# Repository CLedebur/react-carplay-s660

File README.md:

# S660 CarPlay

An open-source CarPlay head unit for the Honda S660, built on a Raspberry Pi Compute Module 4 (CM4) + Oratek TOFU carrier board. CarPlay runs as a web app ([`carplay-web-app`](hardware/path-b/node-CarPlay/), built on [node-CarPlay](https://github.com/rhysmorgan134/node-CarPlay)) in the Pi's own Chromium, full-screen under the `cage` kiosk compositor, customised for the S660's panel, controls, and boot environment.

Hardware assembly, wiring, and enclosure instructions are covered separately. This document is the software-side getting-started guide: how to provision a Pi into a working head unit, and how to develop on it.

## Current status

The Pi's system Chromium **composites on the GPU and decodes the CarPlay H.264 stream in hardware**. Measured 2026-09-12 with CarPlay streaming, Chromium's GPU process holds `/dev/video10`, the CM4's `bcm2835-codec` decoder. Raspberry Pi's Chromium build carries the V4L2 patches, and the web app's WebCodecs decoder picks them up with no extra flags (BUILD_NOTES §8.5, §27.1). The kiosk is on screen about 2.5 s after the kernel starts. Logs from every drive are kept on a dedicated `/persist` partition (§31).

> **Path A retired (2026-10-07).** This repo started as a fork of [react-carplay](https://github.com/rhysmorgan134/react-carplay), an Electron app. Upstream Electron lacks the Pi's GPU/V4L2 patches, so it could only render and decode in software. It has been removed in favour of the web app, which is much faster. The last commit containing it is tagged [`path-a-final`](https://github.com/CLedebur/react-carplay-s660/tree/path-a-final), including its CAN-bus, MOST and key-binding code (BUILD_NOTES §32). You will still see "Path A" and "Path B" in the build notes. That history is kept on purpose.

For the full build history, every non-obvious fix, and the reasoning behind each decision, read [`hardware/BUILD_NOTES.md`](hardware/BUILD_NOTES.md) — it is the source of truth for anything hardware-, boot-, or GPU-related.

For PCB design work with the KiCad MCP server in VS Code/Copilot, see
[`pdb-circuit/README.md`](pdb-circuit/README.md).

# Getting started

This is the fastest path to a working unit and is how the reference build is set up.

## Hardware

- A Raspberry Pi Compute Module 4 flashed with **Raspberry Pi OS Lite (64-bit)**, currently Debian 13 "Trixie", with at least 4GB RAM.
- Oratek TOFU Board [(link)](https://store.oratek.com/products/tofu-electronic-board)
- Oratek M.2 Adapter [(link)](https://store.oratek.com/products/tofu-m-2-key-m-adapter)
- CM4 Heatsink/Fan [(link)](https://pt.aliexpress.com/item/1005002541607239.html)
- Carlinkit CPC200-CCPA/CCPM dongle. This performs the Apple MFi handshake, so an iPhone cannot be plugged directly into the Pi. [(link)](https://www.amazon.es/dp/B0H7GRL6YJ)
- HDMI-e to HDMI cable 0.5m [(example)](https://pt.aliexpress.com/item/1005005903047904.html)
- Honda S660 Option Coupler (required for providing power to the CM4 + board). A Pikaichi TR-196 is ideal if you can find one. Otherwise, you will want a branching coupler so that you can accommodate more peripherals in the future. This is what I got, though I wasn't able to find a branching type coupler: [(example)](https://www.amazon.co.jp/-/en/Pikachi-Power-Supply-Optional-Coupler/dp/B0116HSI40)
- Voltage Converter/Stabilizer (8V-40V to 12V 3A 36W) to provide the board with clean power. [(example)](https://www.amazon.es/dp/B0CPSLSH4J)
- **Not required but highly recommended** - NVMe M.2 SSD (as it will greatly improve boot times and hold up better than an eMMC).
- A MicroSD card (at least 16GB) to flash the Pi OS Lite image onto the CM4. 
- 2.1mm barrel jack AC adapter [(link)](https://www.amazon.es/dp/B09K59PGZ5)
- Wi-Fi Antenna (if you want to use Wi-Fi instead of Ethernet). [(example)](https://www.amazon.es/dp/B08RRX9H2Q)
- 3D-Printed case (pending)

### Assembly

1. Using the standoffs provided by the heatsink/fan kit between the CM4 and the TOFU board, mount the CM4 to the TOFU board. This will allow the heatsink/fan to be mounted on top of the CM4 without bending the CM4.
2. Insert the MicroSD card into the CM4 and flash the Raspberry Pi OS Lite (64-bit) image onto it. You can use [Raspberry Pi Imager](https://www.raspberrypi.com/software/) to do this.
3. Insert the NVMe M.2 SSD into the M.2 adapter first, and then insert onto the TOFU board, and then mount.
4. Connect a monitor to the HDMI port, and a keyboard to the TOFU board. Power on the board and complete the initial setup of the Raspberry Pi OS Lite (64-bit) image. Make sure to enable SSH and set a username and password.
5. Connect the Carlinkit dongle to the USB port on the TOFU board.
6. Run the provisioning script (see below) to install the software and configure the system.

## Software

**Run the provisioning script**, as your normal user (not root, not with `sudo` —
it calls `sudo` itself where needed):

```bash
git clone https://github.com/CLedebur/react-carplay-s660.git
cd react-carplay-s660/hardware
chmod +x provision.sh
./provision.sh
```

This installs the web app as `carplay.service`, enabled to start at boot. The script is safe to re-run after a failure. It ends with **a required reboot**. Starting the kiosk service live (`systemctl start`) does not reliably set up the VT/seat session on first setup. That reboot also runs the one-shot `/persist` repartition (BUILD_NOTES §31), so keep the Pi on stable power for it.

# Physical Installation

## Modifying the head unit

Using plastic trim removal tools, remove the S660's interior parts in this order:

1. Glove box
2. AC vent behind glove box
3. Panels on both sides of the center console in the footwells
4. Remove the plastic shroud behind the center screen, and then unscrew the bolts. Unplug the proprietary HDMI-e cable (gray) and remove the screen.
5. The frame around the stick shift. No need to pull it off entirely, just enough to remove the frame around the center console. The frame is held in place by clips, so be careful not to break them.
6. The tray behind the stick shift. It is held in place with clips. Gently pry the tray up and pull it out. Be careful not to break the clips. Disconnect the cables for the buttons and set aside.
7. The center console itself. It is held in place with clips. Gently pry the front of the console up and pull it out. Be careful not to break the clips. Disconnect the cables for the buttons and set aside.
8. Unscrew the two 10mm bolts securing the head unit to the dashboard. Do not remove, only loosen them.
9. Slide the head unit out sideways; it will slide out of the compartment where the glove box was. Disconnect the cables as you go. Try not to disconnect as many cables you can, as it's very difficult to reconnect them.
10. When you're able to reach it, unplug the HDMI-e cable on the far right side of the head unit (it is the black one) and set aside. Plug in the new HDMI-e cable and route it down to the cavity in the center console behind the shifter.
11. Re-insert the head unit, reconnecting the cables along the way, EXCEPT for the 24-pin harness at the far left. Pull out the harness as much as you can, and then strip away some of the electrical tape to expose around 5mm of the wire coming from pin 22. It will be the light green wire on the bottom left.
12. Cut the wire 5mm from the plug, and then solder the wire from the plug to a small length of wire that will reach a screw on the left side of the head unit. If done correctly, this will bypass the handbrake signal and allow the head unit to work while driving. Make sure to insulate the soldered connection with heat shrink or electrical tape.
13. Plug in the harness and test the head unit. If it works, reassemble the glove box and the AC vent behind it. If it doesn't work, check the soldered connection and make sure the wire is connected to the screw on the left side of the head unit.

## Powering the Pi

1. Wire the 8v-40v to 12v converter to the option coupler. You will want about 1.5m of wire to reach the center console. The converter can be kept in the cavity behind the stick shift. Ensure you connect the positive wire to port number five on the coupler (IGN power). The negative wire will be connected to the chassis ground.
2. Follow [these instructions](https://minkara.carview.co.jp/userid/135377/car/3279425/6972067/note.aspx) to install the option coupler behind the driver's side AC vent.
3. Route the wire behind the carpet. Make sure you secure the wire with zip ties to prevent them from getting caught up in the pedals.
4. Route the wire to the cavity under the center console, and connect to the red/black wire pair on the converter.
5. Connect the industrial connector provided by the TOFU board to the yellow/black wire pair on the converter.
6. Plug in the industrial connecetor to the Pi and start the car to test the power. The Pi should boot up.
7. Switch the input to HDMI via the button on the steering wheel if it isn't there already. The Pi should be running the CarPlay app.

# Works in Progress

1. 3D-printed case for the Pi + TOFU board sized to fit the S660's center console with mounting points.
2. Man-in-the-Middle (MITM) proxy for the physical buttons on the center console so that the buttons and knob can be used to control the CarPlay app ([`hardware/opera-mitm/`](hardware/opera-mitm/), BUILD_NOTES §30).
3. CAN-bus connection, to build vehicle data and the car's own views into the web app.
4. (eventually) A replacement screen for the S660 with touchscreen capabilities and a higher resolution than the stock screen.

# Script Details

**What the script does**, in short (see the script's own comments and
`hardware/BUILD_NOTES.md` §4, §22, §24, and §29 for the full reasoning):

- Trims ~10s off boot by disabling cloud-init, unneeded timers/services, swap, and the
  firmware's own initramfs auto-detection, and by quieting the kernel console.
- Enables Overlay FS: the real root filesystem is mounted read-only underneath a writable
  tmpfs layer, so a hard power cut — this car's normal shutdown path, via ignition, on every
  drive — can't corrupt it. Needs an initramfs to actually run (that's what the auto-detection
  above skips; this one is loaded explicitly instead), which is installed and built during
  provisioning. `/boot/firmware` stays normally writable throughout — verified against a real
  hard power cut (`BUILD_NOTES.md` §29).
- Shrinks root to 64 GiB once and gives the rest of the disk to a `/persist` partition,
  which the overlay does not cover. The systemd journal and the last-known clock live there,
  so every drive's logs survive the ignition cutting power (`BUILD_NOTES.md` §31).
- Installs `cage` (Wayland kiosk compositor) + `seatd`, the udev rule that gives the
  Carlinkit dongle non-root USB/WebUSB access, and a Chromium managed policy that
  pre-grants the dongle to the kiosk page — no on-screen authorisation, ever, even after a
  browser-profile reset (BUILD_NOTES §28).
- Installs system Chromium and builds this repo's vendored `node-CarPlay`/`carplay-web-app`
  source.
- Writes and enables the systemd unit that launches the kiosk on boot.
- Preloads the HDMI component drivers and overlaps the web server and compositor startup.
  (An earlier version of this also shipped an auto-refreshed uncompressed kernel image for
  a further ~2s savings; reverted after a field failure — see `BUILD_NOTES.md` §26.)
- Starts host Bluetooth after 15 s for the trackpad, including when Chromium requests
  BlueZ through D-Bus. Pairing data and the Bluetooth radio remain available.

**By design, networking is requested 20 s after Linux starts**, and timer coalescing
can delay it further. Nothing on the boot-critical path depends on the network,
since Wi-Fi is never guaranteed inside the car. Don't "fix" this; it's intentional.
If the Pi seems unreachable right after a reboot, give it a minute.

## Developing the app

The app source is the `node-carplay` library plus `carplay-web-app`, modified from upstream
[`rhysmorgan134/node-CarPlay`](https://github.com/rhysmorgan134/node-CarPlay) (MIT). It is
vendored directly into this repo at
[`hardware/path-b/node-CarPlay/`](hardware/path-b/node-CarPlay/). It is not a separate
clone or an npm/git dependency. Edit it in place, rebuild, and redeploy by pulling this
repo onto the Pi; the kiosk serves
`~/react-carplay-s660/hardware/path-b/node-CarPlay/examples/carplay-web-app`. See that
directory's own `README.md` and `hardware/BUILD_NOTES.md` §11 and §23 for the exact
build/deploy commands and toolchain gotchas.

**Overlay FS is on in normal use**, so changes made on the Pi vanish at the next power-off.
Turn it off before you deploy (BUILD_NOTES §29), and turn it back on afterwards.

## Thanks

This project builds on [node-carplay](https://github.com/rhysmorgan134/node-CarPlay) and
began as a fork of [react-carplay](https://github.com/rhysmorgan134/react-carplay), both by
Rhys Morgan, with significant CarPlay improvements contributed upstream by @gozmanyoni and
@steelbrain.

If you'd like to show them appreciation, you can [buy gozmanyoni a coffee](https://www.buymeacoffee.com/ygoz) or [buy Rhys a coffee](https://www.buymeacoffee.com/rhysm).

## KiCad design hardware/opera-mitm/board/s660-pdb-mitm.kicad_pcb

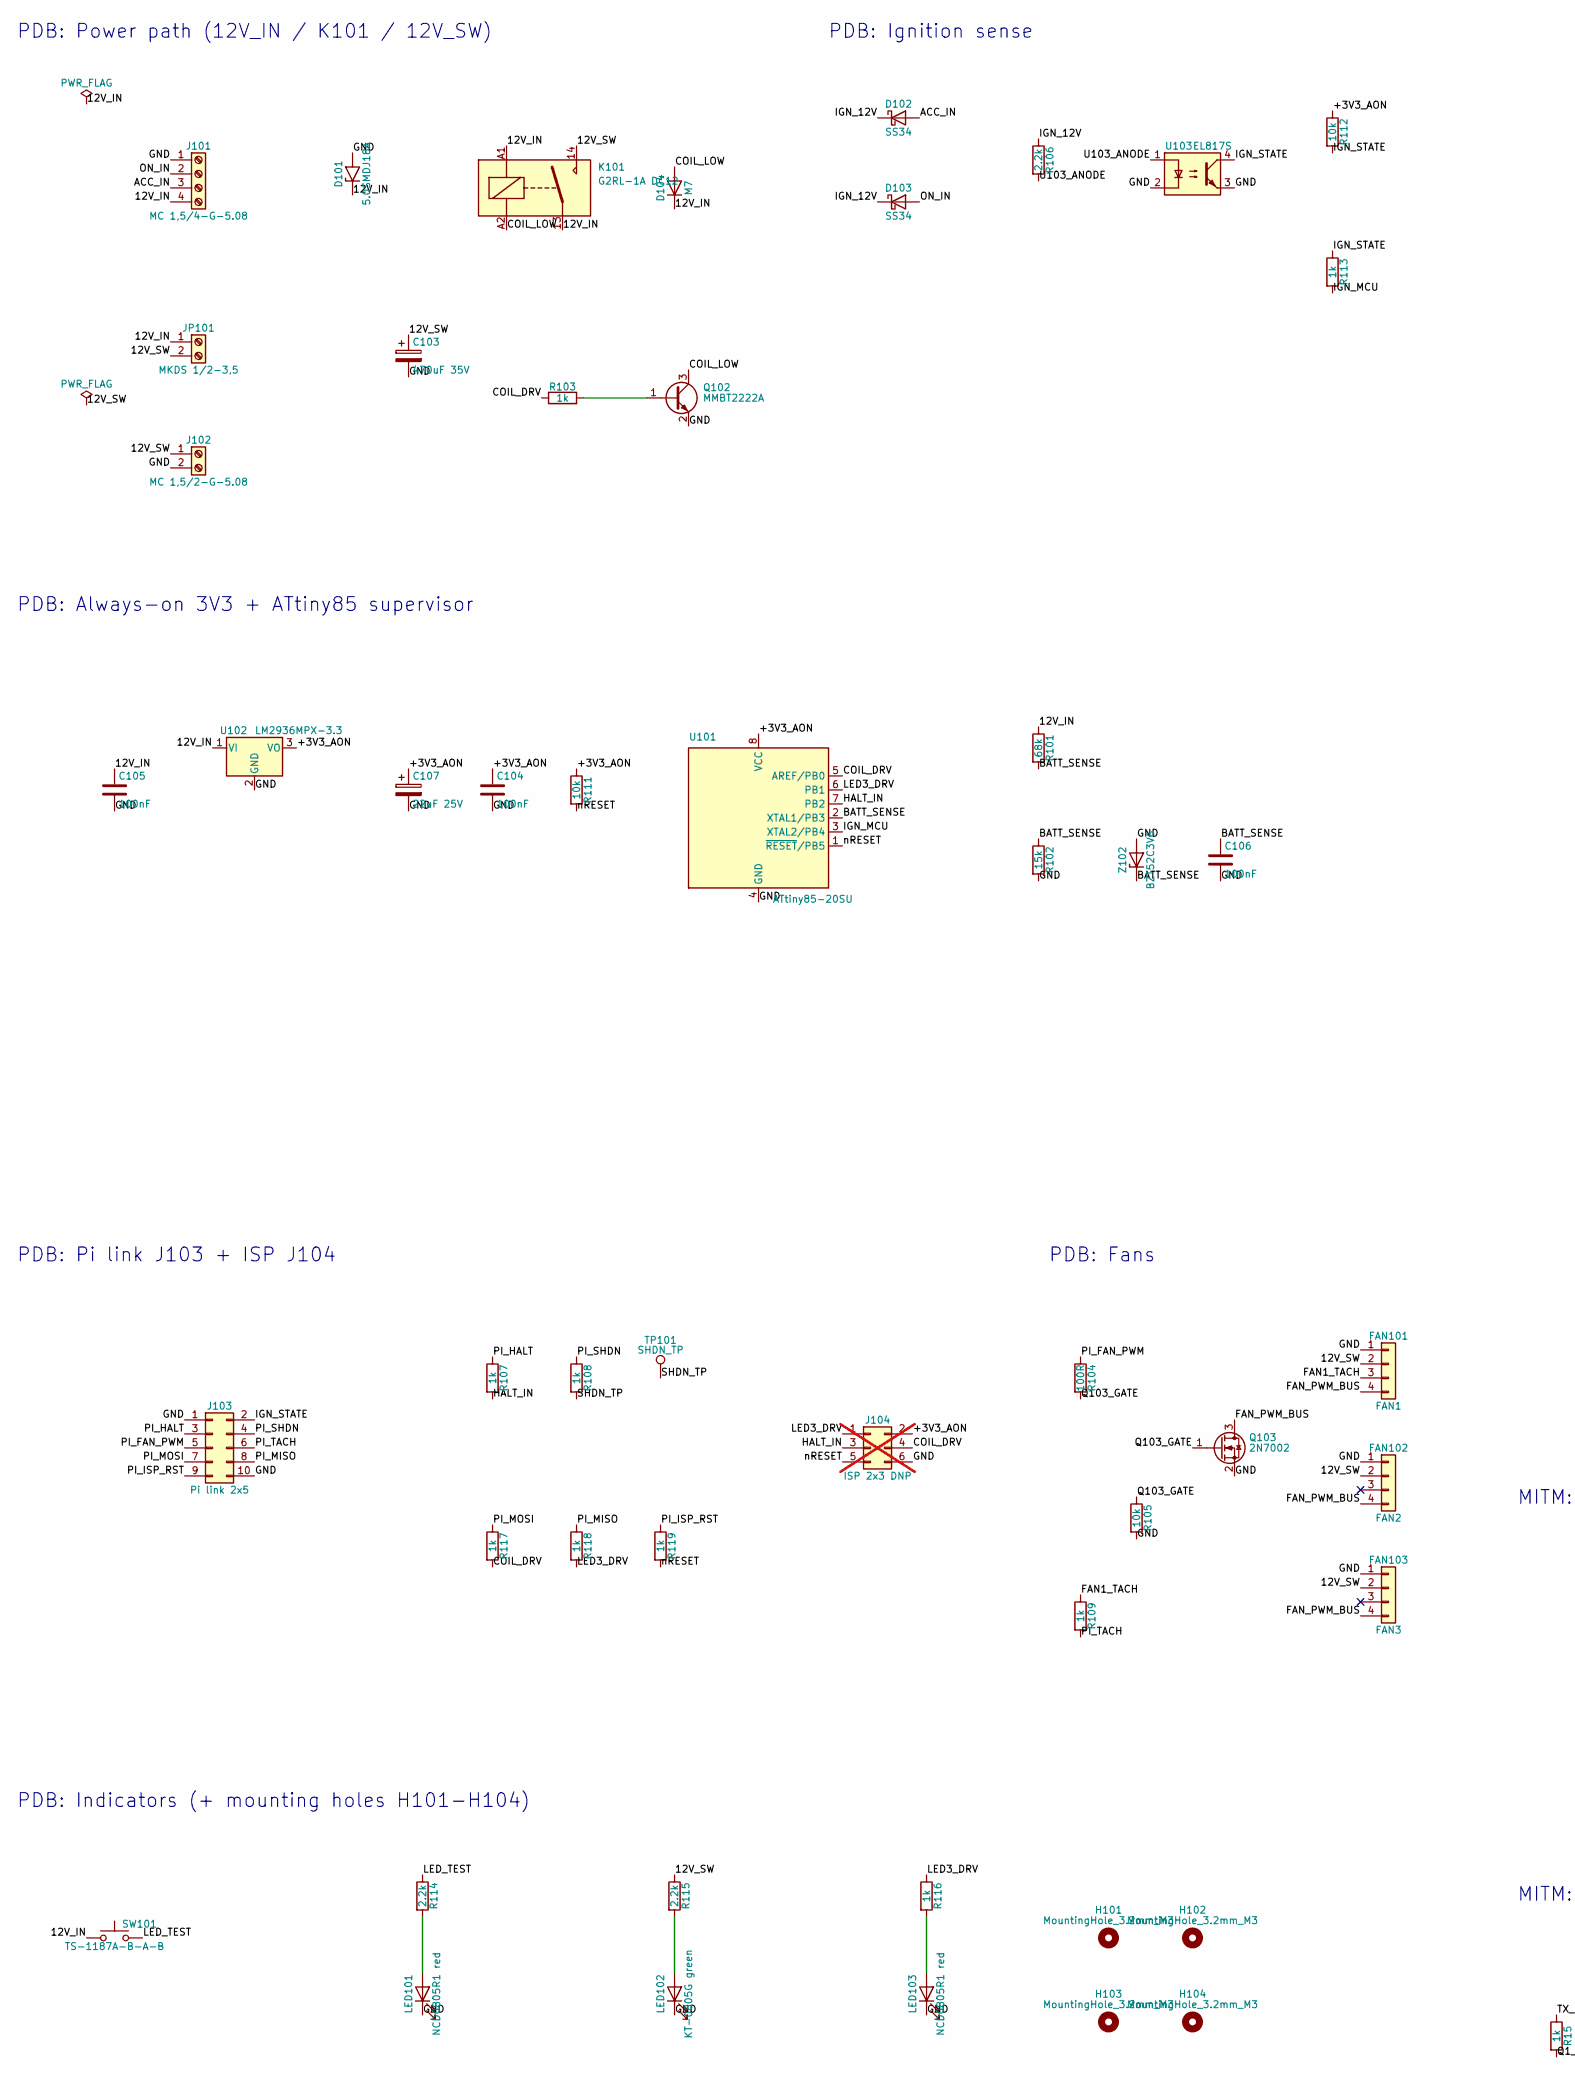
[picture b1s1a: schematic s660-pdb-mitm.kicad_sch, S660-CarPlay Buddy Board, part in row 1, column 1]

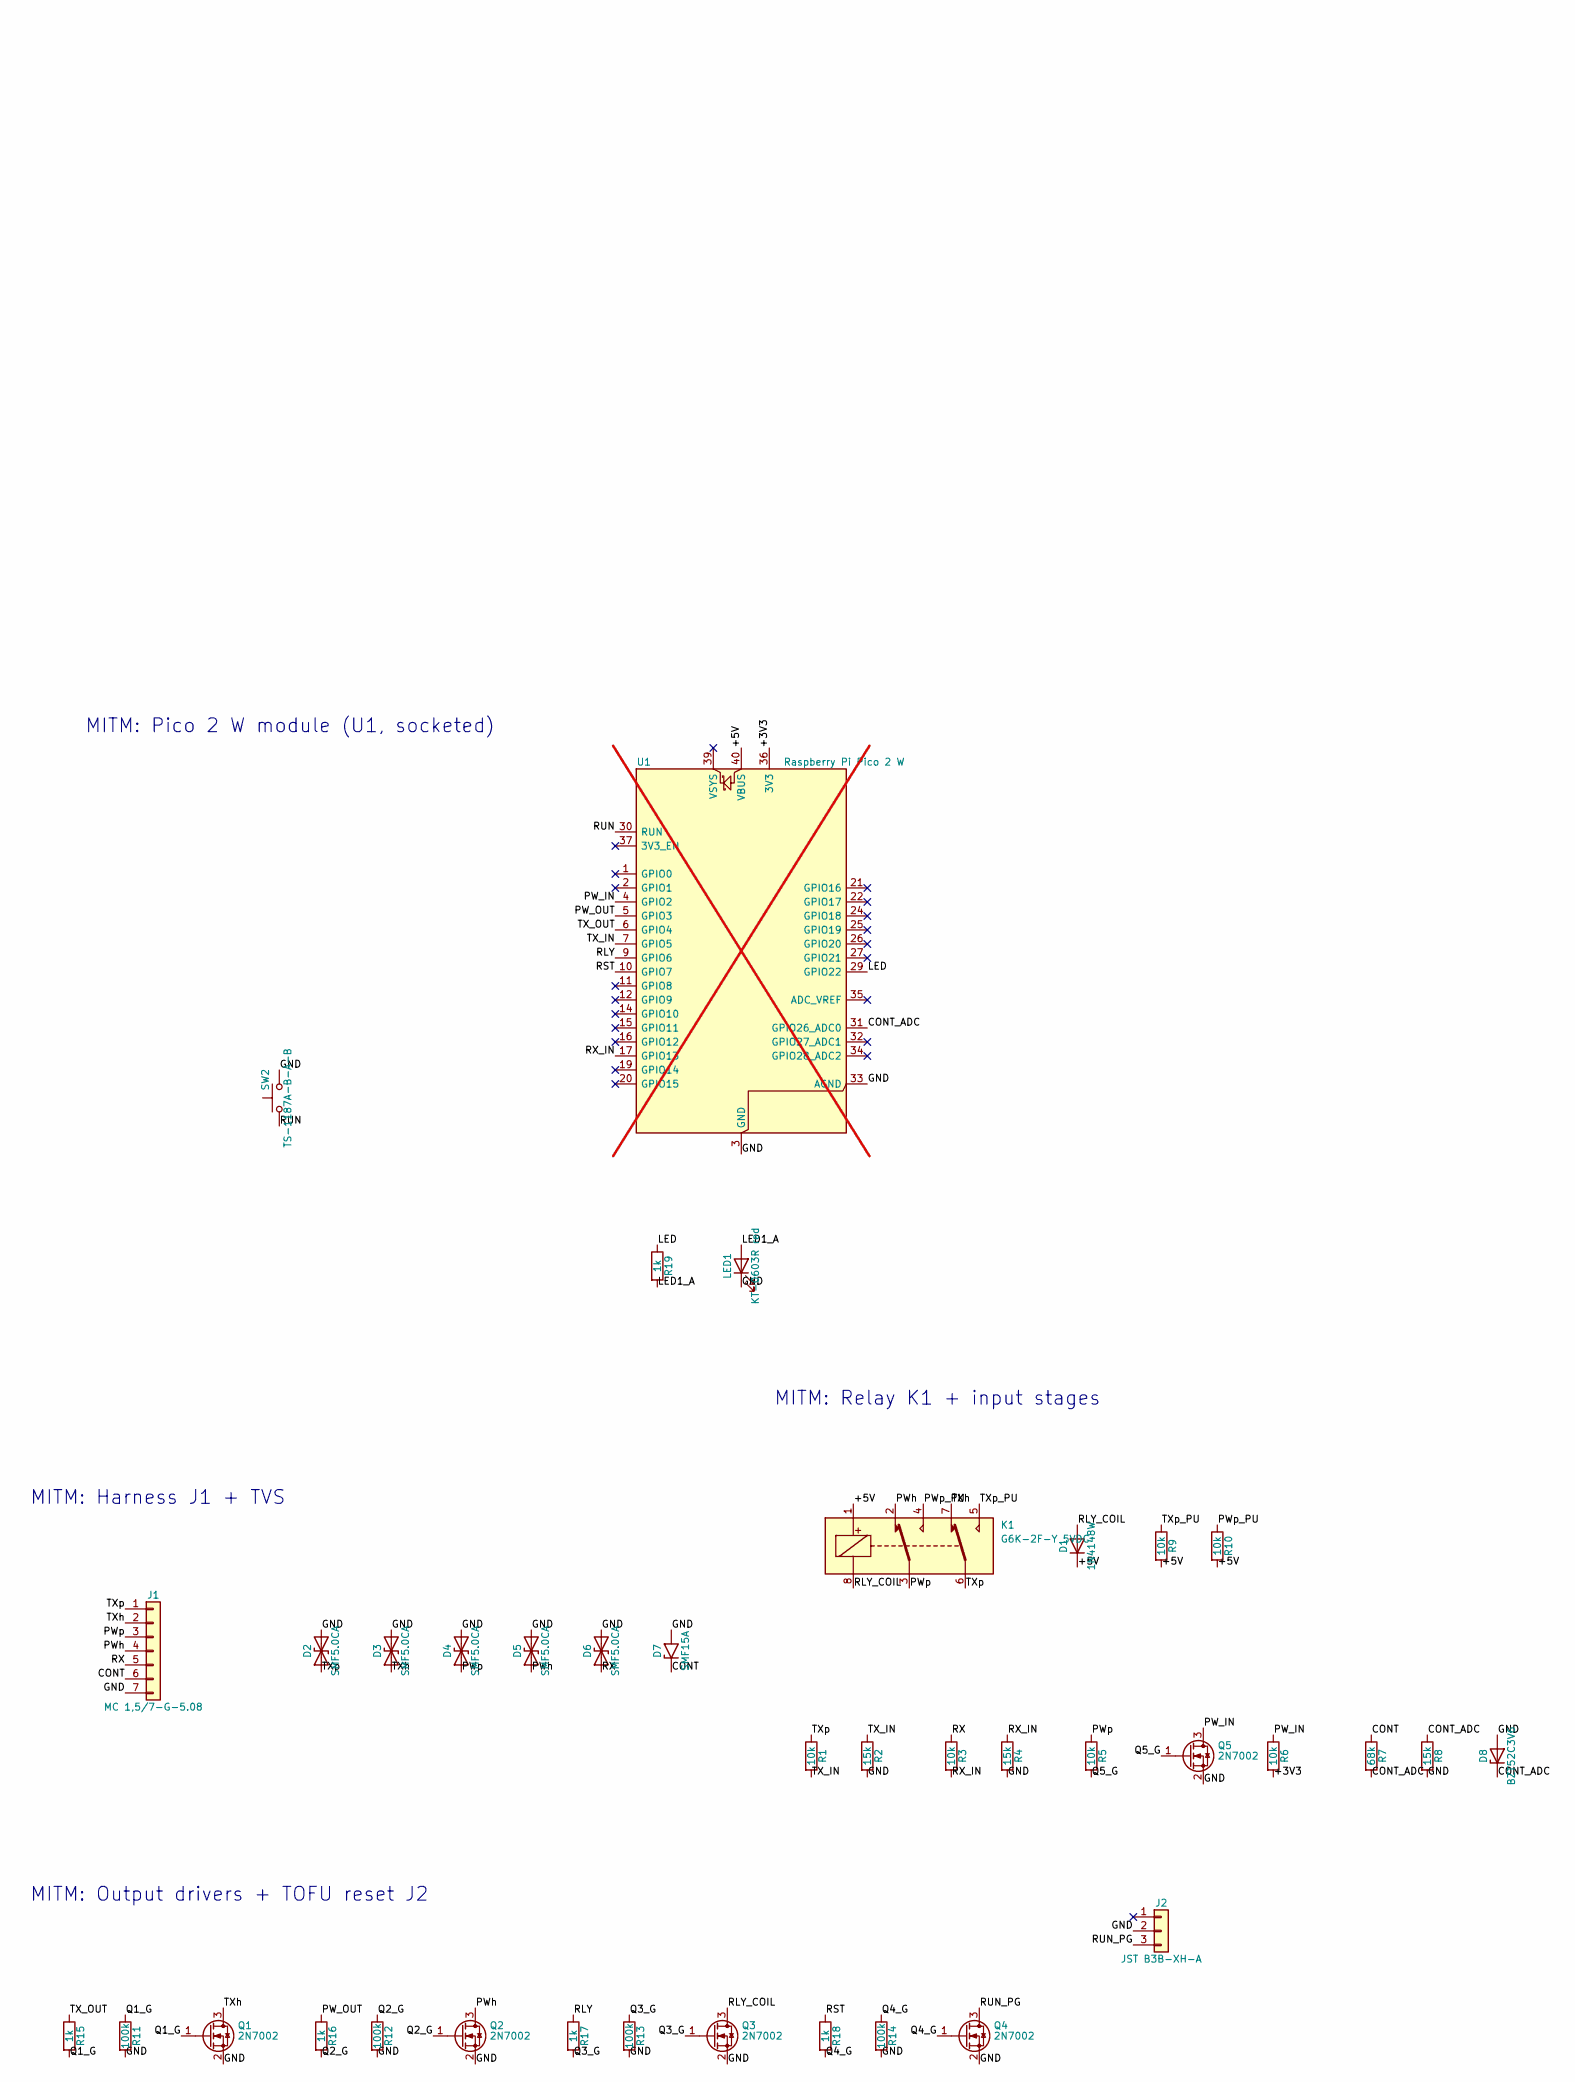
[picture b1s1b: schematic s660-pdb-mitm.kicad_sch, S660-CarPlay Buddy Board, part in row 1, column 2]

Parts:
C103: 470uF 35V; CP_Elec_8x10.5; MPN RV35V470M8X10; LCSC C48935389
C104, C105, C106: 100nF; C_0603_1608Metric; LCSC C14663
C107: 22uF 25V; CP_EIA-6032-28_Kemet-C; MPN TAJC226K025RNJ; LCSC C7214
D1: 1N4148W; D_SOD-123; MPN 1N4148W; LCSC C81598
D2, D3, D4, D5, D6: SMF5.0CA; D_SOD-123F; MPN SMF5.0CA; LCSC C19077498
D7: SMF15A; D_SOD-123F; MPN SMF15A; LCSC C19077509
D8: BZT52C3V6; D_SOD-123; MPN BZT52C3V6; LCSC C19077397
D101: 5.0SMDJ18A; D_SMC; MPN 5.0SMDJ18A; LCSC C2842368
D102, D103: SS34; D_SMA; MPN SS34; LCSC C8678
D104: M7; D_SMA; MPN M7; LCSC C7420350
FAN101: FAN1; PinHeader_1x04_P2.54mm_Horizontal
FAN102: FAN2; PinHeader_1x04_P2.54mm_Horizontal
FAN103: FAN3; PinHeader_1x04_P2.54mm_Horizontal
H101, H102, H103, H104: MountingHole_3.2mm_M3
J1: MC 1,5/7-G-5.08; PhoenixContact_MC_1,5_7-G-5.08_1x07_P5.08mm_Horizontal; MPN MC 1,5/7-G-5.08 (1836231)
J2: JST B3B-XH-A; JST_XH_B3B-XH-A_1x03_P2.50mm_Vertical; MPN B3B-XH-A; LCSC C144394
J101: MC 1,5/4-G-5.08; PhoenixContact_MC_1,5_4-G-5.08_1x04_P5.08mm_Horizontal; MPN MC 1,5/4-G-5.08
J102: MC 1,5/2-G-5.08; PhoenixContact_MC_1,5_2-G-5.08_1x02_P5.08mm_Horizontal; MPN MC 1,5/2-G-5.08
J103: Pi link 2x5; PinHeader_2x05_P2.54mm_Horizontal
J104: ISP 2x3 DNP; PinHeader_2x03_P2.54mm_Vertical; not fitted
JP101: MKDS 1/2-3,5; Phoenix_MKDS_1_2_3.5_1751248; MPN 1751248
K1: G6K-2F-Y 5VDC; Relay_DPDT_Omron_G6K-2F-Y; MPN G6K-2F-Y 5VDC; LCSC C2982926
K101: G2RL-1A DC12; Relay_SPST_Omron_G2RL-1A; MPN G2RL-1A DC12
LED1: KT-0603R red; LED_0603_1608Metric; MPN KT-0603R; LCSC C2286
LED101, LED103: NCD0805R1 red; LED_0805_2012Metric; MPN NCD0805R1; LCSC C84256
LED102: KT-0805G green; LED_0805_2012Metric; MPN KT-0805G; LCSC C2297
Q1, Q2, Q3, Q4, Q5, Q103: 2N7002; SOT-23; MPN 2N7002; LCSC C8545
Q102: MMBT2222A; SOT-23; MPN MMBT2222A; LCSC C8512
R1, R3, R5, R6, R9, R10, R105, R111, R112: 10k; R_0603_1608Metric; LCSC C25804
R2, R4, R8, R102: 15k; R_0603_1608Metric; LCSC C22809
R7, R101: 68k; R_0603_1608Metric; LCSC C23231
R11, R12, R13, R14: 100k; R_0603_1608Metric; LCSC C25803
R15, R16, R17, R18, R19, R103, R107, R108, R109, R113, R116, R117, R118, R119: 1k; R_0603_1608Metric; LCSC C21190
R104: 100R; R_0603_1608Metric; LCSC C22775
R106, R114, R115: 2.2k; R_0603_1608Metric; LCSC C4190
SW2, SW101: TS-1187A-B-A-B; SW_Push_1P1T_XKB_TS-1187A; MPN TS-1187A-B-A-B; LCSC C318884
TP101: SHDN_TP; TestPoint_Pad_D1.5mm
U1: Raspberry Pi Pico 2 W; RaspberryPi_Pico_Common_THT; MPN SC1634; not fitted
U101: ATtiny85-20SU; SOIC-8_5.3x5.3mm_P1.27mm; MPN ATtiny85-20SU; LCSC C31540447
U102: LM2936MPX-3.3; SOT-223-3_TabPin2; MPN LM2936MPX-3.3; LCSC C2872050
U103: EL817S; SOP-4_3.8x4.1mm_P2.54mm; MPN EL817S; LCSC C63268
Z102: BZT52C3V6; D_SOD-123; MPN BZT52C3V6; LCSC C19077397

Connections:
/+3V3: R6.2, U1.36 (3V3)
/+3V3_AON: C104.1, C107.1, J104.2, R111.1, R112.1, U101.8 (VCC), U102.3 (VO)
/+5V: D1.1 (K), K1.1, R9.2, R10.2, U1.40 (VBUS)
/ACC_IN: D102.2 (A), J101.3
/BATT_SENSE: C106.1, R101.2, R102.1, U101.2 (XTAL1/PB3), Z102.1 (K)
/COIL_DRV: J104.4, R103.1, R117.2, U101.5 (AREF/PB0)
/COIL_LOW: D104.2 (A), K101.A2, Q102.3 (C)
/CONT: D7.1 (A1), J1.6, R7.1
/CONT_ADC: D8.1 (K), R7.2, R8.1, U1.31 (GPIO26_ADC0)
/FAN1_TACH: FAN101.3, R109.1
/FAN_PWM_BUS: FAN101.4, FAN102.4, FAN103.4, Q103.3 (D)
/GND: C103.2, C104.2, C105.2, C106.2, C107.2, D2.2 (A2), D3.2 (A2), D4.2 (A2), D5.2 (A2), D6.2 (A2), D7.2 (A2), D8.2 (A), D101.2 (A2), FAN101.1, FAN102.1, FAN103.1, J1.7, J2.2, J101.1, J102.2, J103.1, J103.10, J104.6, LED1.1 (K), LED101.1 (K), LED102.1 (K), LED103.1 (K), Q1.2 (S), Q2.2 (S), Q3.2 (S), Q4.2 (S), Q5.2 (S), Q102.2 (E), Q103.2 (S), R2.2, R4.2, R8.2, R11.2, R12.2, R13.2, R14.2, R102.2, R105.2, SW2.2, U1.3 (GND), U1.8 (GND), U1.13 (GND), U1.18 (GND), U1.23 (GND), U1.28 (GND), U1.33 (AGND), U1.38 (GND), U101.4 (GND), U102.2 (GND), U103.2, U103.3, Z102.2 (A)
/HALT_IN: J104.3, R107.2, U101.7 (PB2)
/IGN_12V: D102.1 (K), D103.1 (K), R106.1
/IGN_MCU: R113.2, U101.3 (XTAL2/PB4)
/IGN_STATE: J103.2, R112.2, R113.1, U103.4
/LED: R19.1, U1.29 (GPIO22)
/LED1_A: LED1.2 (A), R19.2
/LED3_DRV: J104.1, R116.1, R118.2, U101.6 (PB1)
/LED_TEST: R114.1, SW101.2
/ON_IN: D103.2 (A), J101.2
/PI_FAN_PWM: J103.5, R104.1
/PI_HALT: J103.3, R107.1
/PI_ISP_RST: J103.9, R119.1
/PI_MISO: J103.8, R118.1
/PI_MOSI: J103.7, R117.1
/PI_SHDN: J103.4, R108.1
/PI_TACH: J103.6, R109.2
/PW_IN: Q5.3 (D), R6.1, U1.4 (GPIO2)
/PW_OUT: R16.1, U1.5 (GPIO3)
/PWh: D5.1 (A1), J1.4, K1.2, Q2.3 (D)
/PWp: D4.1 (A1), J1.3, K1.3, R5.1
/PWp_PU: K1.4, R10.1
/Q1_G: Q1.1 (G), R11.1, R15.2
/Q2_G: Q2.1 (G), R12.1, R16.2
/Q3_G: Q3.1 (G), R13.1, R17.2
/Q4_G: Q4.1 (G), R14.1, R18.2
/Q5_G: Q5.1 (G), R5.2
/Q103_GATE: Q103.1 (G), R104.2, R105.1
/RLY: R17.1, U1.9 (GPIO6)
/RLY_COIL: D1.2 (A), K1.8, Q3.3 (D)
/RST: R18.1, U1.10 (GPIO7)
/RUN: SW2.1, U1.30 (RUN)
/RUN_PG: J2.3, Q4.3 (D)
/RX: D6.1 (A1), J1.5, R3.1
/RX_IN: R3.2, R4.1, U1.17 (GPIO13)
/SHDN_TP: R108.2, TP101.1 (1_1)
/TX_IN: R1.2, R2.1, U1.7 (GPIO5)
/TX_OUT: R15.1, U1.6 (GPIO4)
/TXh: D3.1 (A1), J1.2, K1.7, Q1.3 (D)
/TXp: D2.1 (A1), J1.1, K1.6, R1.1
/TXp_PU: K1.5, R9.1
/U103_ANODE: R106.2, U103.1
/nRESET: J104.5, R111.2, R119.2, U101.1 (~RESET/PB5)
unnamed: LED101.2 (A), R114.2
unnamed: LED102.2 (A), R115.2
unnamed: LED103.2 (A), R116.2
unnamed: Q102.1 (B), R103.2

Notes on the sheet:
MITM: Output drivers + TOFU reset J2
PDB: Ignition sense
MITM: Pico 2 W module (U1, socketed)
PDB: Fans
PDB: Pi link J103 + ISP J104
MITM: Relay K1 + input stages
MITM: Harness J1 + TVS
PDB: Always-on 3V3 + ATtiny85 supervisor
PDB: Power path (12V_IN / K101 / 12V_SW)
PDB: Indicators (+ mounting holes H101-H104)

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
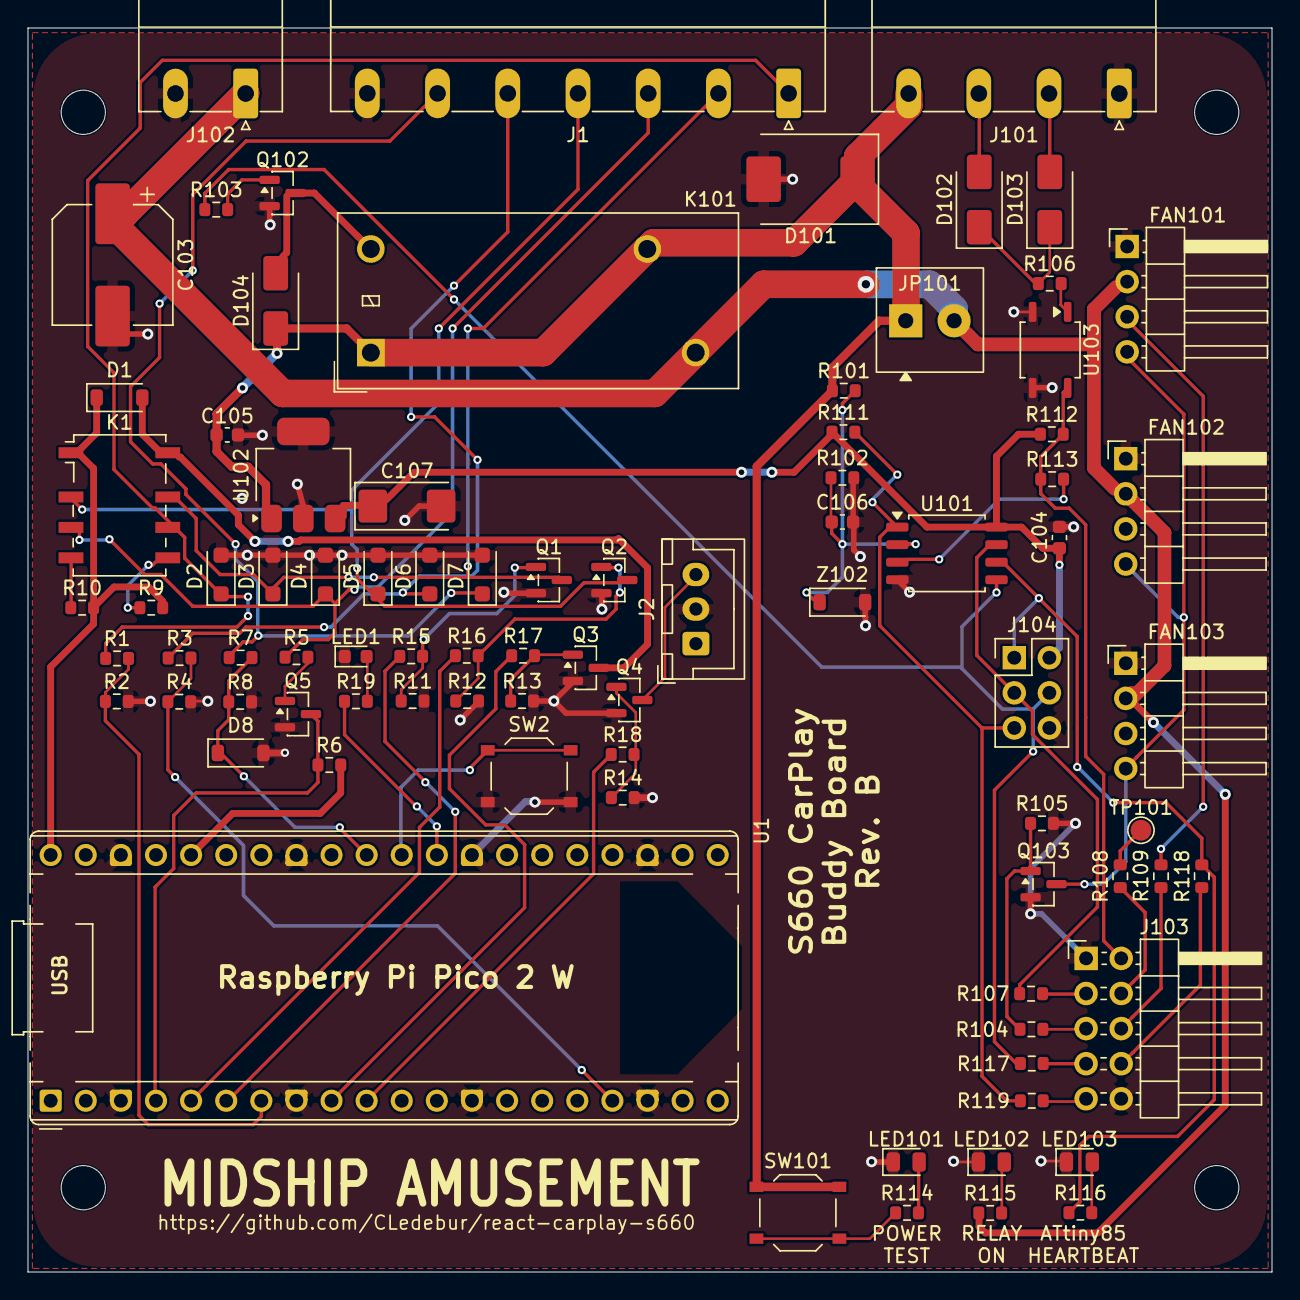
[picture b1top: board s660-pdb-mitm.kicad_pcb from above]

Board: 2 copper layers, 90.0 x 90.0 mm, 89 parts (0 on the bottom side), 60 nets.

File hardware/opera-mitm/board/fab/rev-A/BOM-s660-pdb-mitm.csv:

"Designator","Comment","Footprint","LCSC Part #","MPN","Manufacturer"
"C103","470uF 35V","Capacitor_SMD:CP_Elec_8x10.5","C48935389","RV35V470M8X10",""
"C104,C105,C106","100nF","Capacitor_SMD:C_0603_1608Metric","C14663","",""
"C107","22uF 25V","Capacitor_Tantalum_SMD:CP_EIA-6032-28_Kemet-C","C7214","TAJC226K025RNJ","KYOCERA AVX"
"D1","1N4148W","Diode_SMD:D_SOD-123","C81598","1N4148W",""
"D2,D3,D4,D5,D6","SMF5.0CA","Diode_SMD:D_SOD-123F","C19077498","SMF5.0CA",""
"D7","SMF15A","Diode_SMD:D_SOD-123F","C19077509","SMF15A",""
"D8,Z102","BZT52C3V6","Diode_SMD:D_SOD-123","C19077397","BZT52C3V6",""
"D101","5.0SMDJ18A","Diode_SMD:D_SMC","C2842368","5.0SMDJ18A","Littelfuse"
"D102,D103","SS34","Diode_SMD:D_SMA","C8678","SS34",""
"D104","M7","Diode_SMD:D_SMA","C7420350","M7",""
"FAN101","FAN1","Connector_PinHeader_2.54mm:PinHeader_1x04_P2.54mm_Horizontal","","",""
"FAN102","FAN2","Connector_PinHeader_2.54mm:PinHeader_1x04_P2.54mm_Horizontal","","",""
"FAN103","FAN3","Connector_PinHeader_2.54mm:PinHeader_1x04_P2.54mm_Horizontal","","",""
"H101,H102,H103,H104","MountingHole_3.2mm_M3","MountingHole:MountingHole_3.2mm_M3","","",""
"J1","JST B7B-XH-A","Connector_JST:JST_XH_B7B-XH-A_1x07_P2.50mm_Vertical","C144398","B7B-XH-A","JST"
"J2","JST B3B-XH-A","Connector_JST:JST_XH_B3B-XH-A_1x03_P2.50mm_Vertical","C144394","B3B-XH-A","JST"
"J101","MC 1,5/4-G-5.08","Connector_Phoenix_MC_HighVoltage:PhoenixContact_MC_1,5_4-G-5.08_1x04_P5.08mm_Horizontal","","MC 1,5/4-G-5.08","Phoenix Contact"
"J102","MC 1,5/2-G-5.08","Connector_Phoenix_MC_HighVoltage:PhoenixContact_MC_1,5_2-G-5.08_1x02_P5.08mm_Horizontal","","MC 1,5/2-G-5.08","Phoenix Contact"
"J103","Pi link 2x5","Connector_PinHeader_2.54mm:PinHeader_2x05_P2.54mm_Horizontal","","",""
"JP101","MKDS 1/2-3,5","s660-pdb-mitm:Phoenix_MKDS_1_2_3.5_1751248","","1751248","Phoenix Contact"
"K1","G6K-2F-Y 5VDC","Relay_SMD:Relay_DPDT_Omron_G6K-2F-Y","C2982926","G6K-2F-Y 5VDC","Omron"
"K101","G2RL-1A DC12","Relay_THT:Relay_SPST_Omron_G2RL-1A","","G2RL-1A DC12","Omron"
"LED1","KT-0603R red","LED_SMD:LED_0603_1608Metric","C2286","KT-0603R",""
"LED101,LED103","NCD0805R1 red","LED_SMD:LED_0805_2012Metric","C84256","NCD0805R1",""
"LED102","KT-0805G green","LED_SMD:LED_0805_2012Metric","C2297","KT-0805G",""
"Q1,Q2,Q3,Q4,Q5,Q103","2N7002","Package_TO_SOT_SMD:SOT-23","C8545","2N7002",""
"Q102","MMBT2222A","Package_TO_SOT_SMD:SOT-23","C8512","MMBT2222A",""
"R1,R3,R5,R6,R9,R10,R105,R111,R112","10k","Resistor_SMD:R_0603_1608Metric","C25804","",""
"R2,R4,R8,R102","15k","Resistor_SMD:R_0603_1608Metric","C22809","",""
"R7,R101","68k","Resistor_SMD:R_0603_1608Metric","C23231","",""
"R11,R12,R13,R14","100k","Resistor_SMD:R_0603_1608Metric","C25803","",""
"R15,R16,R17,R18,R19,R103,R107,R108,R109,R113,R116,R117,R118,R119","1k","Resistor_SMD:R_0603_1608Metric","C21190","",""
"R104","100R","Resistor_SMD:R_0603_1608Metric","C22775","",""
"R106,R114,R115","2.2k","Resistor_SMD:R_0603_1608Metric","C4190","",""
"SW2,SW101","TS-1187A-B-A-B","Button_Switch_SMD:SW_Push_1P1T_XKB_TS-1187A","C318884","TS-1187A-B-A-B","XKB"
"TP101","SHDN_TP","TestPoint:TestPoint_Pad_D1.5mm","","",""
"U1","Raspberry Pi Pico 2 W","Module:RaspberryPi_Pico_Common_THT","","SC1634","Raspberry Pi"
"U101","ATtiny85-20SU","Package_SO:SOIC-8_5.3x5.3mm_P1.27mm","C31540447","ATtiny85-20SU","Microchip"
"U102","LM2936MPX-3.3","Package_TO_SOT_SMD:SOT-223-3_TabPin2","C2872050","LM2936MPX-3.3","Texas Instruments"
"U103","EL817S","Package_SO:SOP-4_3.8x4.1mm_P2.54mm","C63268","EL817S","Everlight"
